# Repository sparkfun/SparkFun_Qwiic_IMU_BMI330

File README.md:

-------------------------------------------------

The [SparkFun 6DoF IMU Breakout - BMI330 (Qwiic)](https://www.sparkfun.com/sparkfun-6dof-imu-breakout-bmi330-qwiic.html) is a compact, 6-axis inertial measurement unit (IMU) breakout built around the Bosch BMI330. The BMI330 combines a 16-bit triaxial accelerometer and a 16-bit triaxial gyroscope in a single low-power package, making it a great choice for motion tracking, orientation sensing, gesture recognition, and wearable applications.

Designed for our [Qwiic ecosystem](https://www.sparkfun.com/qwiic), the board breaks out the BMI330 over I2C so you can add high-quality motion sensing to your project without any soldering. An onboard programmable interrupt engine handles features like any/no-motion detection, tap and step detection, and orientation recognition directly on the sensor, freeing up your host microcontroller. The two Qwiic connectors let you daisy-chain the board with the rest of your Qwiic devices, and the standard breakout footprint also exposes the I2C and interrupt pins for use with SPI or a solderless breadboard.

## Repository Contents

* **/Documents** - Datasheets, additional product information
* **/Hardware** - KiCad design files (.kicad_sch, .kicad_pcb, .kicad_pro)

## Documentation

* **[Hookup Guide](https://docs.sparkfun.com/SparkFun_Qwiic_IMU_BMI330/)** - Basic hookup guide for the SparkFun 6DoF IMU Breakout - BMI330 (Qwiic).
* **[SparkFun BMI330 Arduino Library](https://github.com/sparkfun/SparkFun_BMI330_Arduino_Library)** - An Arduino library for the SparkFun 6DoF IMU Breakout - BMI330 (Qwiic).

## Product Versions

* **[SEN-31767](https://www.sparkfun.com/sparkfun-6dof-imu-breakout-bmi330-qwiic.html)** - Initial release of the SparkFun 6DoF IMU Breakout - BMI330 (Qwiic).

## License Information

This product is _**open source**_!

Please review the LICENSE.md file for license information.

If you have any questions or concerns about licensing, please contact technical support on our [SparkFun forums](https://forum.sparkfun.com/viewforum.php?f=152).

Distributed as-is; no warranty is given.

_- Your friends at SparkFun._

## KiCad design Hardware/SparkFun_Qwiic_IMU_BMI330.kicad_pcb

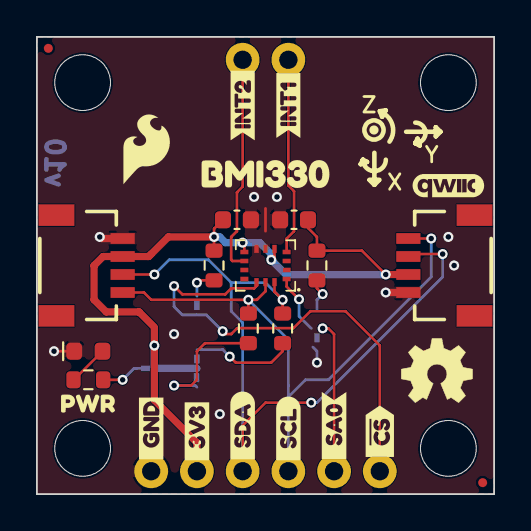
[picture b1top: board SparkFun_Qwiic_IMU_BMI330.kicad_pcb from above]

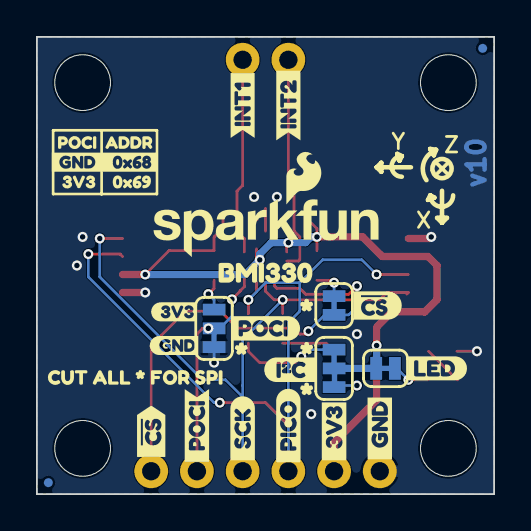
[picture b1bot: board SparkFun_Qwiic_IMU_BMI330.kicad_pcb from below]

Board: 2 copper layers, 25.4 x 25.4 mm, 60 parts (29 on the bottom side), 14 nets.

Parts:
C3, C4: 0.1uF; C_0603_1608Metric
D1: Red; LED_0603_1608Metric_Red
FID1, FID2, FID3, FID4: Fiducial_0.5mm; Fiducial_0.5mm_Mask1mm
G4: OSHW_Logo; Creative_Commons_License
J1, J2: Qwiic_RA; JST_1x04_P1.0mm_Horizontal_SMD
J3: Conn_01x06; 1x06_P2.54mm
J4: Conn_01x02; 1x02_P2.54mm
JP1: LED; Jumper_2_NC_Trace
JP2: I²C; Jumper_3_NC-2_Trace
JP3: ~{CS}; Jumper_2_NC_Trace
JP4: ADDR; Jumper_3_NC-1_Trace
R1, R2: 10k; R_0603_1608Metric
R3: 4.7k; R_0603_1608Metric
R4, R5: 2.2k; R_0603_1608Metric
Ref**: Val**; OSHW_Logo_4mm
ST1, ST2, ST3, ST4: Standoff
U1: BMI330; ST_LGA-14L_2.5x3.0mm_P0.5mm_4x3
kibuzzard-6A2AF6B9: G***; kibuzzard-6A2AF6B9
kibuzzard-6A2AF6DB: G***; kibuzzard-6A2AF6DB
kibuzzard-6A2C6EC9: G***; kibuzzard-6A2C6EC9
kibuzzard-6A2C6F4B, kibuzzard-6A2C6F4B#2: G***; kibuzzard-6A2C6F4B
kibuzzard-6A2C6F56, kibuzzard-6A2C6F56#2: G***; kibuzzard-6A2C6F56
kibuzzard-6A399BFC: G***; kibuzzard-6A399BFC
kibuzzard-6A399D1E: G***; kibuzzard-6A399D1E
kibuzzard-6A399D08: G***; kibuzzard-6A399D08
kibuzzard-6A399D19: G***; kibuzzard-6A399D19
kibuzzard-6A3997C3, kibuzzard-6A3997C3#2, kibuzzard-6A3997C3#3, kibuzzard-6A3997C3#4: G***; kibuzzard-6A3997C3
kibuzzard-6A34231C: G***; kibuzzard-6A34231C
kibuzzard-6A39953E: G***; kibuzzard-6A39953E
kibuzzard-6A39988E: G***; kibuzzard-6A39988E
kibuzzard-6A39993E: G***; kibuzzard-6A39993E
kibuzzard-6A39994B: G***; kibuzzard-6A39994B
kibuzzard-6A343325: G***; kibuzzard-6A343325
kibuzzard-6A399819: G***; kibuzzard-6A399819
kibuzzard-6A399897: G***; kibuzzard-6A399897
kibuzzard-6A399913: G***; kibuzzard-6A399913
kibuzzard-6A399936: G***; kibuzzard-6A399936
kibuzzard-69FCD097: G***; kibuzzard-69FCD097
kibuzzard-689A66E2: G***; kibuzzard-689A66E2
kibuzzard-689A66E9: G***; kibuzzard-689A66E9
kibuzzard-689A66EE: G***; kibuzzard-689A66EE
kibuzzard-689A642E: G***; kibuzzard-689A642E
kibuzzard-689A6721: G***; kibuzzard-689A6721
kibuzzard-689A6728: G***; kibuzzard-689A6728
kibuzzard-689A6796: G***; kibuzzard-689A6796

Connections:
3.3V: C3.1, C4.1, J1.2, J2.2, J3.2, JP1.2 (B), JP2.2 (B), R1.2, R2.2, U1.5 (VDDIO), U1.8 (VDD)
GND: C3.2, C4.2, D1.1 (K), J1.1, J2.1, J3.1, JP4.1 (A), U1.6 (GND), U1.7 (GND)
INT1: J4.1, U1.4 (INT1)
INT2: J4.2, U1.9 (INT2)
unnamed: D1.2 (A), R3.1
unnamed: JP1.1 (A), R3.2
unnamed: JP2.1 (A), R5.2
unnamed: JP2.3 (C), R4.2
unnamed: JP3.2 (B), R2.1
unnamed: JP4.3 (C), R1.1
SCL: J1.4, J2.4, J3.4, R4.1, U1.13 (SCL)
SDA/PICO: J1.3, J2.3, J3.3, R5.1, U1.14 (SDA)
SDO/POCI: J3.5, JP4.2 (B), U1.1 (SDO)
~CS: J3.6, JP3.1 (A), U1.12 (~CS)

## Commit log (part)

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2026-06-17 Added datasheet
2026-06-22 Updated designs based on design review
    - Nudged traces and vias
    - Centered PTH
    - Added Silkscreen for I2C/SPI
2026-06-23 Changed IC PROD_ID and updated silk to v10

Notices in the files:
parts and their libraries:
Released under the Creative Commons Attribution Share-Alike 4.0 License
https://creativecommons.org/licenses/by-sa/4.0
